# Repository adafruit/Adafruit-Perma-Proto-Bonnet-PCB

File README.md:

## Adafruit Perma Proto Bonnet PCB

<a href="http://www.adafruit.com/products/3203"><br/>
Click here to purchase one from the Adafruit shop</a>

PCB files for the Adafruit Perma Proto Bonnet for Raspberry Pi. Format is EagleCAD schematic and board layout
* https://www.adafruit.com/products/3203

### Description

Design your own Bonnet or pHAT, attach custom circuitry and otherwise dress your Pi Zero with this jaunty prototyping Bonnet kit!

To add to the [Adafruit Bonnet party](https://www.adafruit.com/categories/929), we have this Perma-Proto inspired plug in daughter board. It has a grid of 0.1" prototyping soldering holes for attaching chips, resistors, LED, potentiometers and more. The holes are connected underneath with traces to mimic the solderless breadboards with which you're familiar. There's also long power strips for +3V, +5V and Ground connections to the Pi. Near the top we break out nearly every pin you could want to connect to the Pi (#26 didn't quite make the cut).

The __Perma-Proto Bonnet__ comes with a printed circuit board and a single [2x20 GPIO Header for Raspberry Pi](http://www.adafruit.com/product/2222) to put your Perma-Proto on top of your Raspberry Pi Zero (like a nice little bonnet...). Unlike our [Perma-Proto HATs](https://www.adafruit.com/products/2314), this design does not include an EEPROM, so you can 'stack' it with other Bonnets and pHATs without worrying about an EEPROM address collision.

You can customize your Perma-Proto setup using a [standard 2x20 stacking header](https://www.adafruit.com/products/2223) or [extra tall 2x20 stacking header](https://www.adafruit.com/product/1979).

You can also swap out the 2x20 header with a [slim 2x20 type if you want it to sit closer to the Pi](https://www.adafruit.com/products/2243), or [an extra tall one if you want it to sit above the USB/Ethernet ports](https://www.adafruit.com/products/1992).

A bit of light soldering is required to attach the header to the PCB but it's easy work.

This bonnet is designed for use with Raspberry Pi Zero but you can put on top of any Raspberry Pi with a 2x20 connector, it will just not stick out as far. [We also offer a full 'HAT' sized version for Pi A+, B+, Pi 2 & 3.](https://www.adafruit.com/products/2310)

### License

Adafruit invests time and resources providing this open source design, please support Adafruit and open-source hardware by purchasing products from [Adafruit](https://www.adafruit.com)!

Designed by Limor Fried/Ladyada for Adafruit Industries.

Creative Commons Attribution/Share-Alike, all text above must be included in any redistribution. See license.txt for additional details.

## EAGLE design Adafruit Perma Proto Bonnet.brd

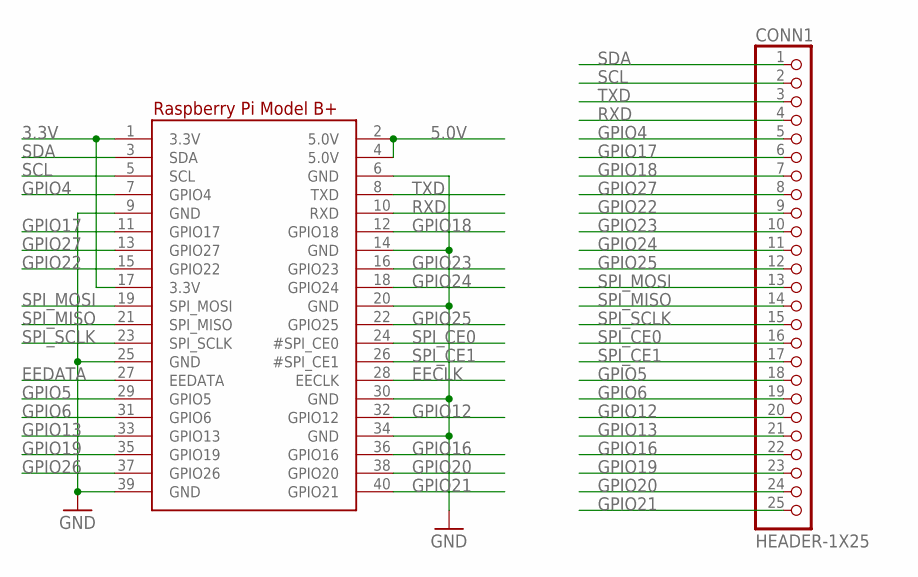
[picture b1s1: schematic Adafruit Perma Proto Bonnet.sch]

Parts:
CONN1: HEADER-1X25; 1X25_ROUND_70MIL
RPI1: RASPBERRYPI_BPLUS_BONNETNODIM; PI_BONNET_NODIM

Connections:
3.3V: RPI1.1 (3.3V), RPI1.17 (3.3V)
5.0V: RPI1.2 (5.0V), RPI1.4 (5.0V)
EECLK: RPI1.28 (EECLK)
EEDATA: RPI1.27 (EEDATA)
GND: RPI1.6 (GND), RPI1.9 (GND), RPI1.14 (GND), RPI1.20 (GND), RPI1.25 (GND), RPI1.30 (GND), RPI1.34 (GND), RPI1.39 (GND)
GPIO4: CONN1.5, RPI1.7 (GPIO4)
GPIO5: CONN1.18, RPI1.29 (GPIO5)
GPIO6: CONN1.19, RPI1.31 (GPIO6)
GPIO12: CONN1.20, RPI1.32 (GPIO12)
GPIO13: CONN1.21, RPI1.33 (GPIO13)
GPIO16: CONN1.22, RPI1.36 (GPIO16)
GPIO17: CONN1.6, RPI1.11 (GPIO17)
GPIO18: CONN1.7, RPI1.12 (GPIO18)
GPIO19: CONN1.23, RPI1.35 (GPIO19)
GPIO20: CONN1.24, RPI1.38 (GPIO20)
GPIO21: CONN1.25, RPI1.40 (GPIO21)
GPIO22: CONN1.9, RPI1.15 (GPIO22)
GPIO23: CONN1.10, RPI1.16 (GPIO23)
GPIO24: CONN1.11, RPI1.18 (GPIO24)
GPIO25: CONN1.12, RPI1.22 (GPIO25)
GPIO26: RPI1.37 (GPIO26)
GPIO27: CONN1.8, RPI1.13 (GPIO27)
RXD: CONN1.4, RPI1.10 (RXD)
SCL: CONN1.2, RPI1.5 (SCL)
SDA: CONN1.1, RPI1.3 (SDA)
SPI_CE0: CONN1.16, RPI1.24 (#SPI_CE0)
SPI_CE1: CONN1.17, RPI1.26 (#SPI_CE1)
SPI_MISO: CONN1.14, RPI1.21 (SPI_MISO)
SPI_MOSI: CONN1.13, RPI1.19 (SPI_MOSI)
SPI_SCLK: CONN1.15, RPI1.23 (SPI_SCLK)
TXD: CONN1.3, RPI1.8 (TXD)

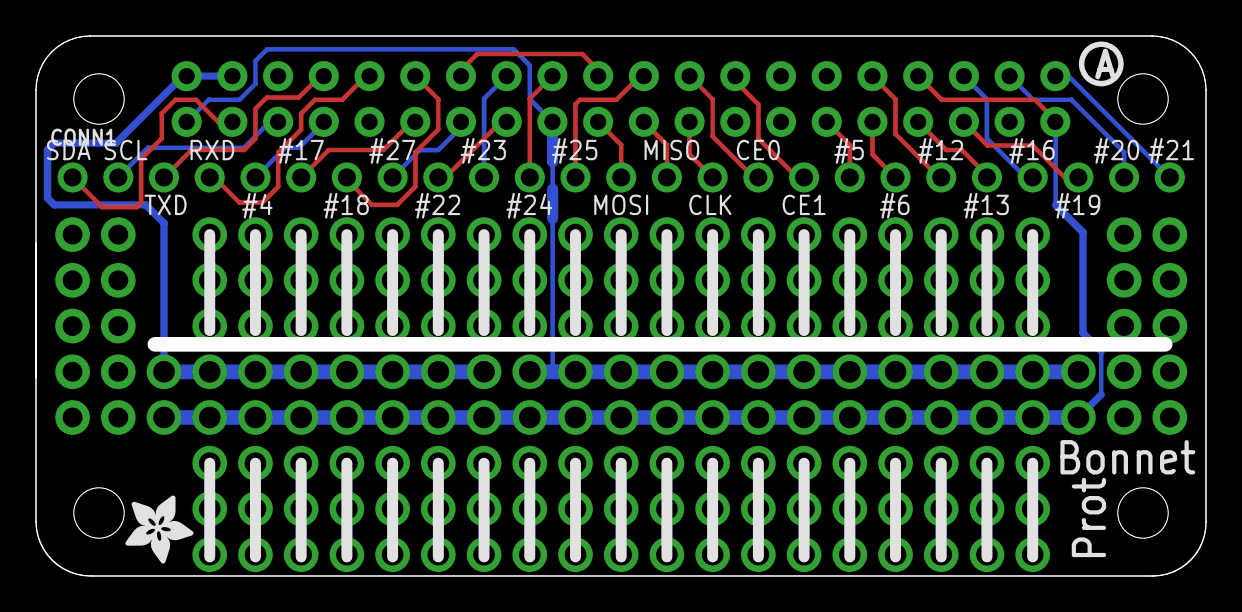
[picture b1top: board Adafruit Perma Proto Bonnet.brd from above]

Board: 2 copper layers, 65.0 x 30.0 mm, 4 parts (0 on the bottom side), 28 nets.

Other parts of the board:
U$1: ADAFRUIT_3.5MM
U$3: PCBFEAT-REV-056

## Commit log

2017-03-13 init
2019-08-29 fixed readme

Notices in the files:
parts and their libraries:
microbuilder: This work is placed in the public domain, and may be freely used for commercial and non-commercial work with the following conditions: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
